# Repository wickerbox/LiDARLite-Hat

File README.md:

# LiDARLite-Hat
A simple datalogging hat for the LiDAR-Lite rangefinder from PulsedLight3D.

### Getting Started

The primary reference is the <a href="https://github.com/PulsedLight3D/LIDAR-Lite-Documentation/raw/master/Docs/LIDAR-Lite-v1-docs.pdf">LiDAR-Lite v1 Operating Manual</a>. 

The board and the rangefinder must be connected by a custom jumper. The length of the jumper must be as short as possible. The mating connector to the LiDAR-Lite is Molex P/N 5023800600 (Digikey P/N WM2271-ND).

The board must sit against the back of the unit. The board must be shaped according to page 12 of the manual. It may be double sided, in which case it must sit on spacers. 

The schematic and layout must be created in KiCad. The board must be licensed under CERN's Open Hardware License v1.2, and any test code must be licensed under the GPL v3. 

The LiDAR-Lite supports PWM and I2C communication; therefore, the microcontroller must support both methods of communication. 

The board must include the following:

- an Arduino-compatible microcontroller 
- a micro-USB connector 
- a micro-SD card for logging 
- all input/output pins exposed on breakout headers
- voltage regulation to provide 3.3V from the 5V USB input 
- heartbeat LED 
- 2x3 ICSP header broken out for programming bootloader

The board must be programmable directly from Arduino IDE over a USB cable.

EEPROM may be used on the microcontroller for persistent information.

### Block Diagram

I make a block diagram on my way to figuring out which microcontroller to use. 

### Setting up the KiCAD Project

Before grabbing a project template, I'll need to decide on my board fabricator (for my design rules) and whether I'm making a 2-layer or 4-layer board. I'm using OSH Park and going with a four-layer board. 1.4x1.9 is 2.66 square inches, or $26.60 for a set of three four-layer boards. That's about $9 per board. It would only be $4.50 per board but I think layout's going to really be tight so I'm going with $9 for the first prototype.

Therefore, I'm using my <a href="https://github.com/wickerbox/wickerlib/tree/master/templates/oshpark-4layer">OSH Park 4-layer template</a>. 

### Microcontroller

I dropped in all of the circuits I'll need for the sections so I can see which microcontroller I need.

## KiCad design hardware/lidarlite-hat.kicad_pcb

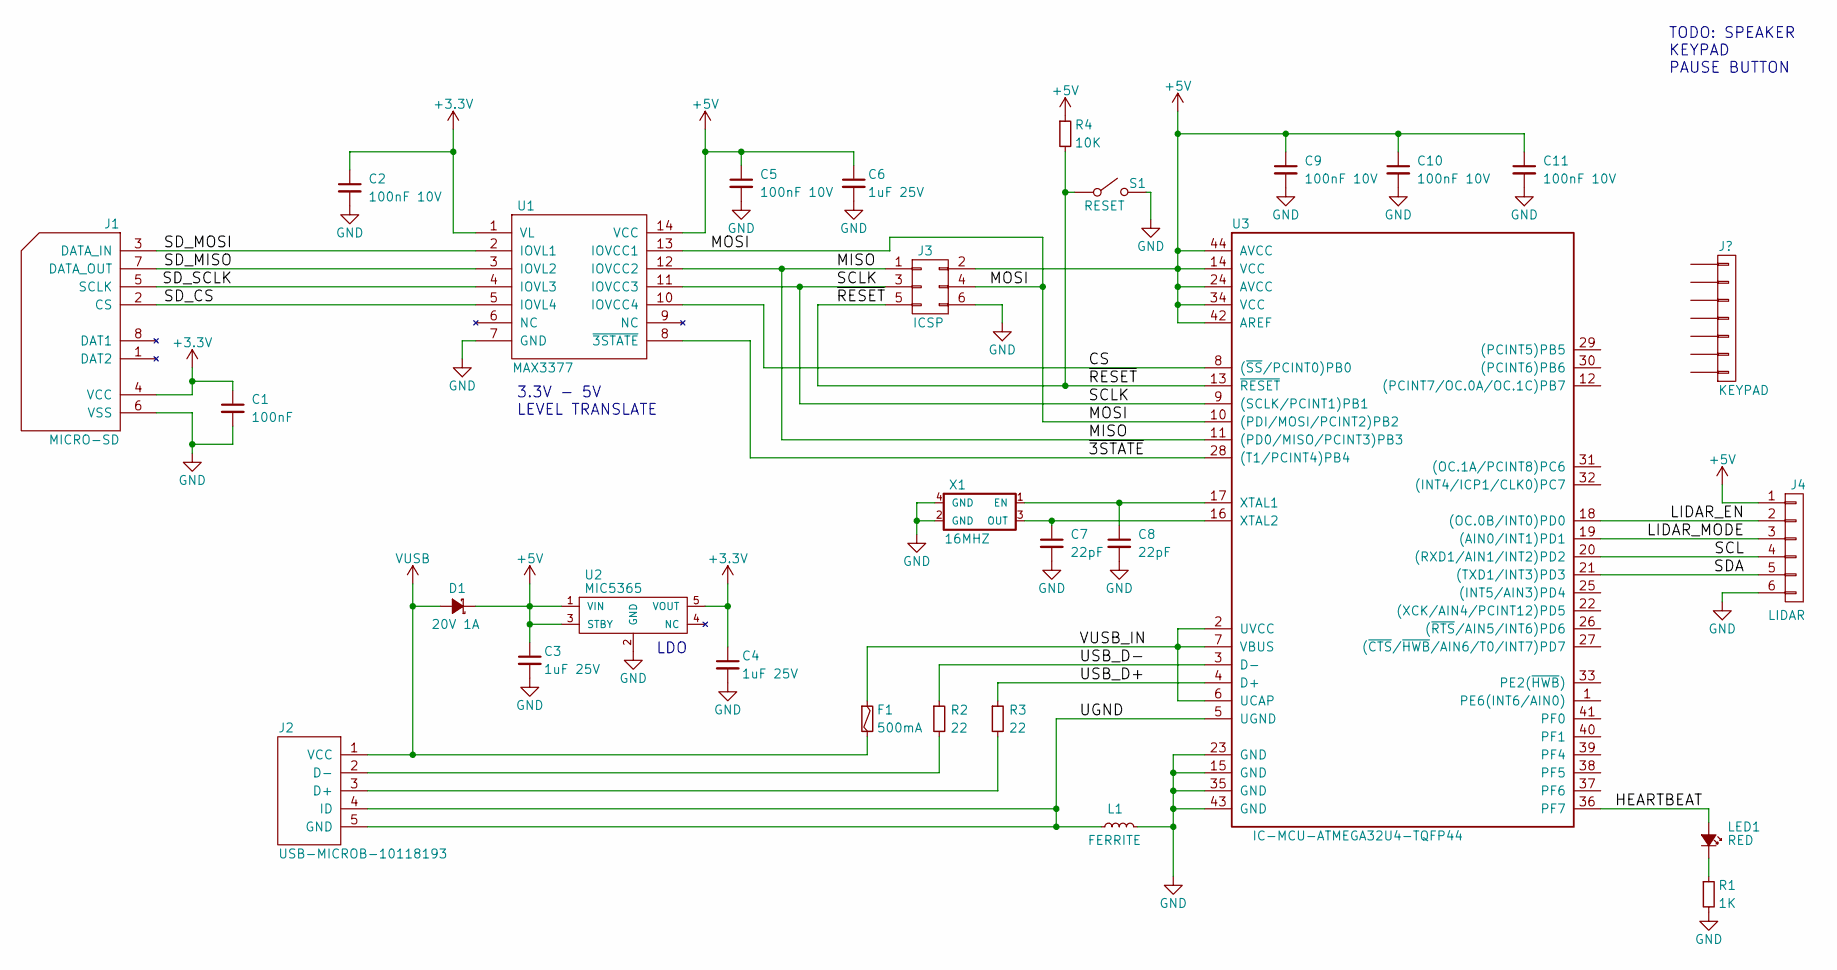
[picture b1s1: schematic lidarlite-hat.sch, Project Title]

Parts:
C1: 100nF; 0402
C2, C5, C9, C10, C11: 100nF 10V; 0402
C3, C4, C6: 1uF 25V; 0603
C7, C8: 22pF; 0603
D1: 20V 1A; Diode_SMA
F1: 500mA; 1812
J1: MICRO-SD; Conn_uSDcard
J2: USB-MICROB-10118193; USB-Micro-B-10118193_0001LF
J3: ICSP; Pin_Header_Straight_2x03
J4: LIDAR; Pin_Header_Straight_1x06
L1: FERRITE; 0402
LED1: RED; 0603
R1: 1K; 0603
R2, R3: 22; 0603
R4: 10K; 0603
S1: RESET; SW-B3U-1000P
U1: MAX3377; TSSOP-14_4.4x5mm_Pitch0.65mm
U2: MIC5365; SOT-23-5
U3: IC-MCU-ATMEGA32U4-TQFP44; TQFP-44_10x10mm_Pitch0.8mm
X1: 16MHZ; CRYSTAL-CTS-4SMD

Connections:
+3V3: C1.1, C2.1, C4.1, J1.4 (VCC), U1.1 (VL), U2.5 (VOUT)
+5V: C3.1, C5.1, C6.1, C9.1, C10.1, C11.1, D1.1 (K), J3.2, J4.1, R4.1, U1.14 (VCC), U2.1 (VIN), U2.3 (STBY), U3.14 (VCC), U3.24 (AVCC), U3.34 (VCC), U3.42 (AREF), U3.44 (AVCC)
/CS: U1.10 (IOVCC4), U3.8 ((~SS~/PCINT0)PB0)
/HEARTBEAT: LED1.2 (A), U3.36 (PF7)
/LIDAR_EN: J4.2, U3.18 ((OC.0B/INT0)PD0)
/LIDAR_MODE: J4.3, U3.19 ((AIN0/INT1)PD1)
/MISO: J3.1, U1.12 (IOVCC2), U3.11 ((PD0/MISO/PCINT3)PB3)
/MOSI: J3.4, U1.13 (IOVCC1), U3.10 ((PDI/MOSI/PCINT2)PB2)
/SCL: J4.4, U3.20 ((RXD1/AIN1/INT2)PD2)
/SCLK: J3.3, U1.11 (IOVCC3), U3.9 ((SCLK/PCINT1)PB1)
/SDA: J4.5, U3.21 ((TXD1/INT3)PD3)
/SD_CS: J1.2 (CS), U1.5 (IOVL4)
/SD_MISO: J1.7 (DATA_OUT), U1.3 (IOVL2)
/SD_MOSI: J1.3 (DATA_IN), U1.2 (IOVL1)
/SD_SCLK: J1.5 (SCLK), U1.4 (IOVL3)
/UGND: J2.4 (ID), J2.5 (GND), L1.1, U3.5 (UGND)
/USB_D+: R3.1, U3.4 (D+)
/USB_D-: R2.1, U3.3 (D-)
/VUSB_IN: F1.1, U3.2 (UVCC), U3.6 (UCAP), U3.7 (VBUS)
/~3STATE: U1.8 (~3STATE), U3.28 ((T1/PCINT4)PB4)
/~RESET: J3.5, R4.2, S1.1, U3.13 (~RESET)
GND: C1.2, C2.2, C3.2, C4.2, C5.2, C6.2, C7.2, C8.2, C9.2, C10.2, C11.2, J1.6 (VSS), J3.6, J4.6, L1.2, R1.2, S1.2, U1.7 (GND), U2.2 (GND), U3.15 (GND), U3.23 (GND), U3.35 (GND), U3.43 (GND), X1.2 (GND), X1.4 (GND)
unnamed: C7.1, U3.16 (XTAL2), X1.3 (OUT)
unnamed: C8.1, U3.17 (XTAL1), X1.1 (EN)
unnamed: J2.2 (D-), R2.2
unnamed: J2.3 (D+), R3.2
unnamed: LED1.1 (K), R1.1
VUSB: D1.2 (A), F1.2, J2.1 (VCC)

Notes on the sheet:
LDO
3.3V - 5V LEVEL TRANSLATE
TODO: SPEAKER KEYPAD PAUSE BUTTON

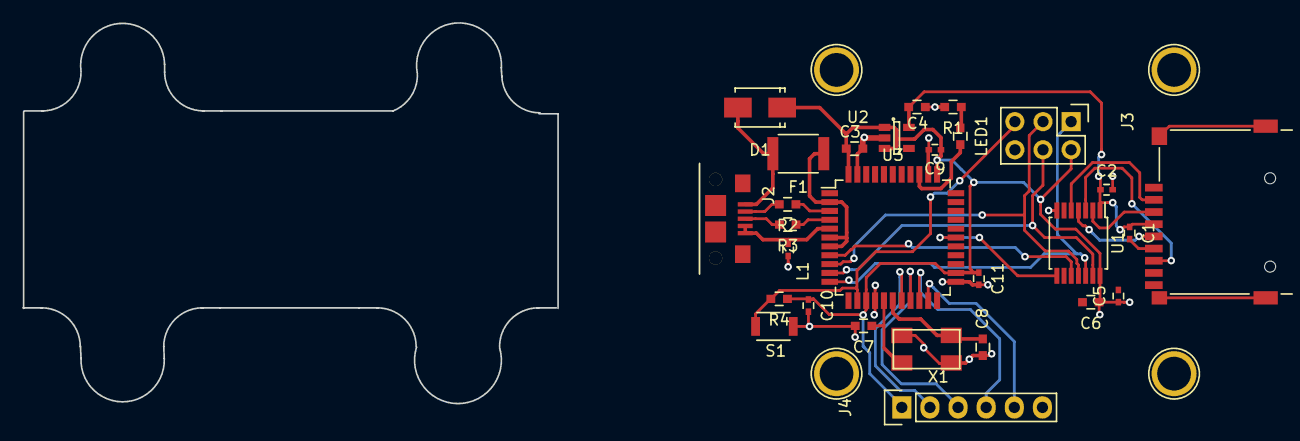
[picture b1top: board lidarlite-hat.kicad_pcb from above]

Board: 2 copper layers, 48.3 x 34.4 mm, 32 parts (0 on the bottom side), 28 nets.

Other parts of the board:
P7, P7#2, P7#3, P7#4: CONN_1; ARDUINO-MOUNTING-HOLE

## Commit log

2016-07-06 First hour of design.
2016-07-06 Added power line to LiDAR unit on block diagram.
2016-07-06 Fixed lies.
2016-07-06 Added KiCad project.
2016-07-06 Added microSD circuit.
2016-07-08 In progress. Just playing around.
2016-10-11 Some hardware adds.
2017-10-06 Saving.

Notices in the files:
hardware/lidarlite-hat.kicad_pcb:
Released under the CERN Open Hardware License v1.2
